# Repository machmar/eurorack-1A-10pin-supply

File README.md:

# eurorack-1A-10pin-supply
This is a eurorack PSU which uses two 3A PWM regulators like [these from Aliexpress](https://www.aliexpress.com/item/1005004052885353.html?spm=a2g0o.productlist.0.0.695838edDr9Fcs&algo_pvid=d174f836-2c64-4925-bf83-09754ddc93be&algo_exp_id=d174f836-2c64-4925-bf83-09754ddc93be-3&pdp_ext_f=%7B%22sku_id%22%3A%2212000027872810881%22%7D&pdp_npi=2%40dis%21CZK%21%2119.72%21%21%21%21%21%400b0a555916520957518301529e174a%2112000027872810881%21sea) and outputs +-12V DC.  
The output is only a 10 pin power bus.  
As the power source, use a AC transformer with two 12V or 15V secondary windings.  

As for the old files in this repo (1A PSU). I've disgned them over 4 years ago and back then I had no idea how to make good PCBs (not saying this new PCB is something amazing). I feel bad deleting them so I'll leave them here but **DO NOT BUILD THE OLD FILES!**.

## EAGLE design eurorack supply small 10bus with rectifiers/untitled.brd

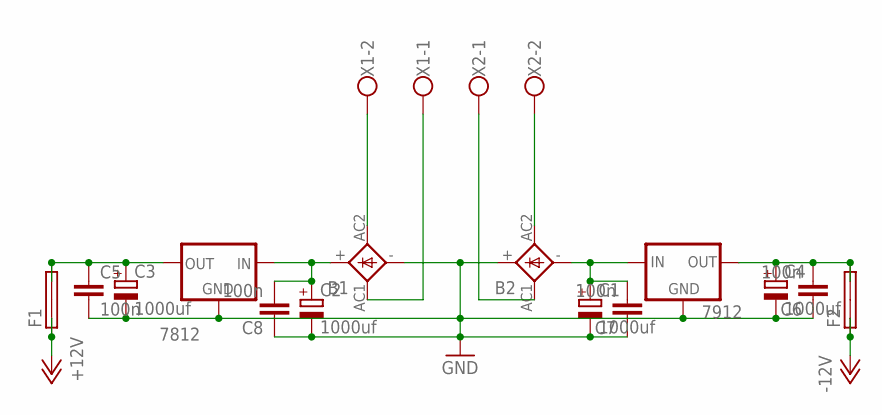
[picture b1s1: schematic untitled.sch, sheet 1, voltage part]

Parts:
7812: 79XXS
7912: 78XXS
B1, B2: FB15
C1, C2, C3, C4: 1000uf; TT5D11
C5, C6, C7, C8: 100n; C075-032X103
F1, F2: SHK20L
X1, X2: W237-102

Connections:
+12V: F1.1A, F1.1B; also elsewhere on the board
-12V: F2.1A, F2.1B; also elsewhere on the board
GND: 7812.GND, 7912.GND, B1.-, B2.+, C1.-, C2.-, C3.-, C4.-, C5.2, C6.1, C7.1, C8.1; also elsewhere on the board
unnamed: 7912.IN, B2.-, C1.+, C7.2
unnamed: 7812.IN, B1.+, C2.+, C8.2
unnamed: 7912.OUT, C4.+, C6.2, F2.2A, F2.2B
unnamed: 7812.OUT, C3.+, C5.1, F1.2A, F1.2B
unnamed: B1.AC2, X1.2
unnamed: B2.AC2, X2.2
unnamed: B1.AC1, X1.1
unnamed: B2.AC1, X2.1

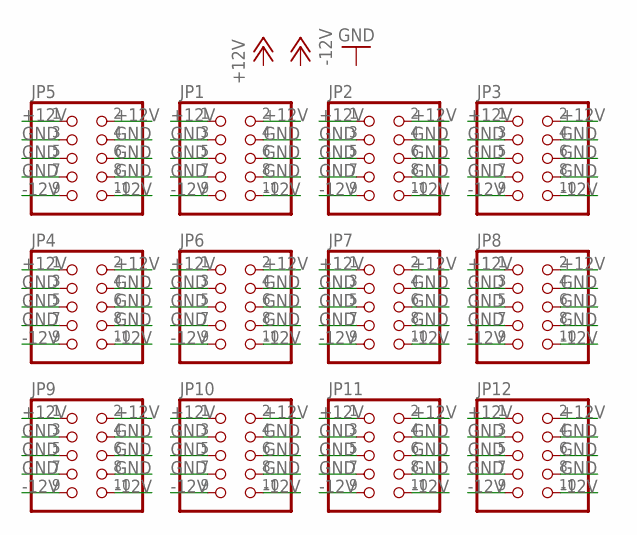
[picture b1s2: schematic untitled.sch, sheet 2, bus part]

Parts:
JP1, JP2, JP3, JP4, JP5, JP6, JP7, JP8, JP9, JP10, JP11, JP12: PINHD-2X5; 2X05

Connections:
+12V: JP1.1, JP1.2, JP2.1, JP2.2, JP3.1, JP3.2, JP4.1, JP4.2, JP5.1, JP5.2, JP6.1, JP6.2, JP7.1, JP7.2, JP8.1, JP8.2, JP9.1, JP9.2, JP10.1, JP10.2, JP11.1, JP11.2, JP12.1, JP12.2; also elsewhere on the board
-12V: JP1.9, JP1.10, JP2.9, JP2.10, JP3.9, JP3.10, JP4.9, JP4.10, JP5.9, JP5.10, JP6.9, JP6.10, JP7.9, JP7.10, JP8.9, JP8.10, JP9.9, JP9.10, JP10.9, JP10.10, JP11.9, JP11.10, JP12.9, JP12.10; also elsewhere on the board
GND: JP1.3, JP1.4, JP1.5, JP1.6, JP1.7, JP1.8, JP2.3, JP2.4, JP2.5, JP2.6, JP2.7, JP2.8, JP3.3, JP3.4, JP3.5, JP3.6, JP3.7, JP3.8, JP4.3, JP4.4, JP4.5, JP4.6, JP4.7, JP4.8, JP5.3, JP5.4, JP5.5, JP5.6, JP5.7, JP5.8, JP6.3, JP6.4, JP6.5, JP6.6, JP6.7, JP6.8, JP7.3, JP7.4, JP7.5, JP7.6, JP7.7, JP7.8, JP8.3, JP8.4, JP8.5, JP8.6, JP8.7, JP8.8, JP9.3, JP9.4, JP9.5, JP9.6, JP9.7, JP9.8, JP10.3, JP10.4, JP10.5, JP10.6, JP10.7, JP10.8, JP11.3, JP11.4, JP11.5, JP11.6, JP11.7, JP11.8, JP12.3, JP12.4, JP12.5, JP12.6, JP12.7, JP12.8; also elsewhere on the board

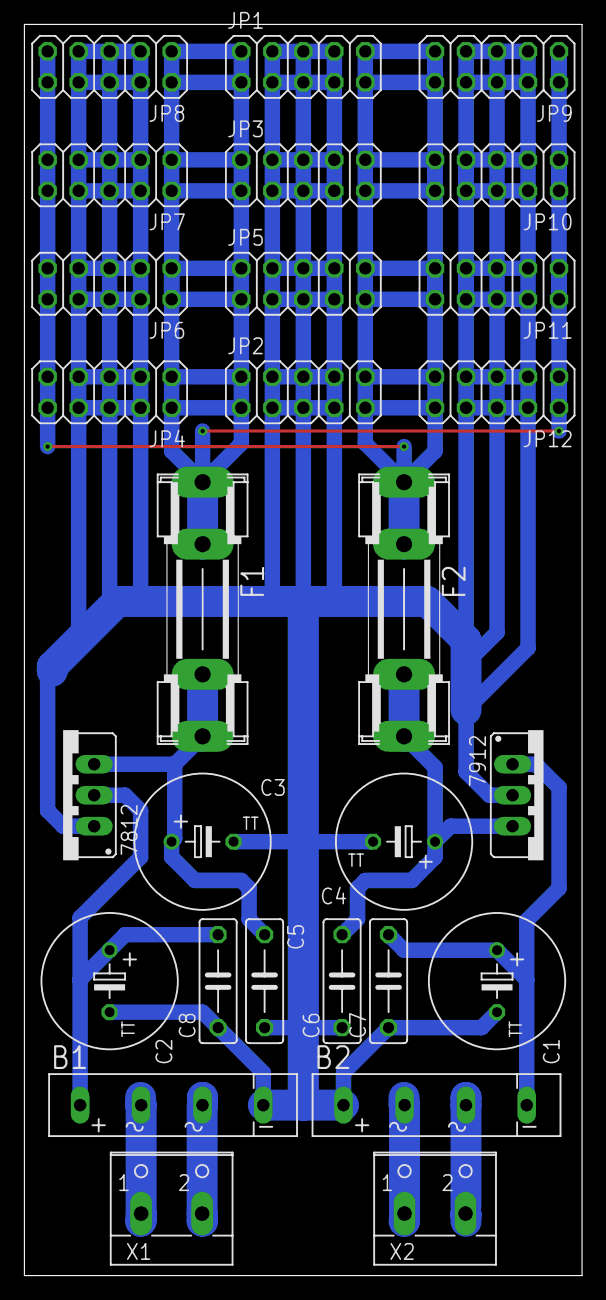
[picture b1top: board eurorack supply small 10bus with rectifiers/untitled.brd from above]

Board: 2 copper layers, 45.7 x 102.5 mm, 28 parts (0 on the bottom side), 11 nets.

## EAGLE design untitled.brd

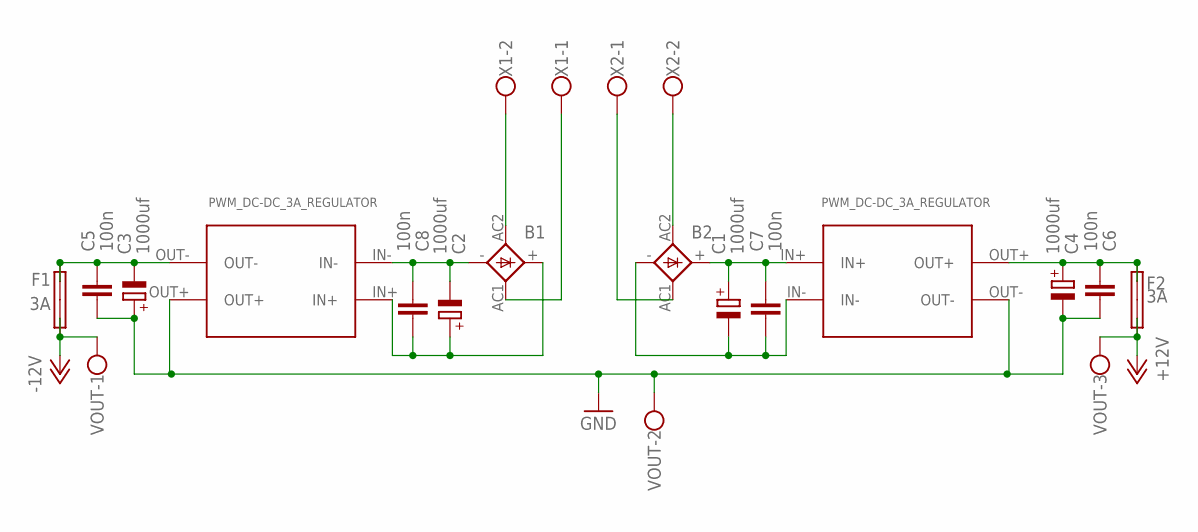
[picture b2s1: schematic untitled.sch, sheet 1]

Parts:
B1, B2: FB15
C1, C2, C3, C4: 1000uf; TT5D11
C5, C6, C7, C8: 100n; C075-032X103
F1, F2: 3A; SHK20L
PWM_DC-DC_3A_REGULATOR1, PWM_DC-DC_3A_REGULATOR2: CP8-ADJ
VOUT: W237-103
X1, X2: W237-102

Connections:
+12V: F2.1A, F2.1B, VOUT.3; also elsewhere on the board
-12V: F1.1A, F1.1B, VOUT.1; also elsewhere on the board
GND: C3.+, C4.-, C5.2, C6.1, PWM_DC-DC_3A_REGULATOR1.OUT+, PWM_DC-DC_3A_REGULATOR2.OUT-, VOUT.2; also elsewhere on the board
unnamed: B2.+, C1.+, C7.2, PWM_DC-DC_3A_REGULATOR2.IN+
unnamed: B1.-, C2.-, C8.2, PWM_DC-DC_3A_REGULATOR1.IN-
unnamed: B2.-, C1.-, C7.1, PWM_DC-DC_3A_REGULATOR2.IN-
unnamed: C4.+, C6.2, F2.2A, F2.2B, PWM_DC-DC_3A_REGULATOR2.OUT+
unnamed: C3.-, C5.1, F1.2A, F1.2B, PWM_DC-DC_3A_REGULATOR1.OUT-
unnamed: B1.AC2, X1.2
unnamed: B2.AC2, X2.2
unnamed: B1.AC1, X1.1
unnamed: B2.AC1, X2.1
unnamed: B1.+, C2.+, C8.1, PWM_DC-DC_3A_REGULATOR1.IN+

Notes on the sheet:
PWM_DC-DC_3A_REGULATOR

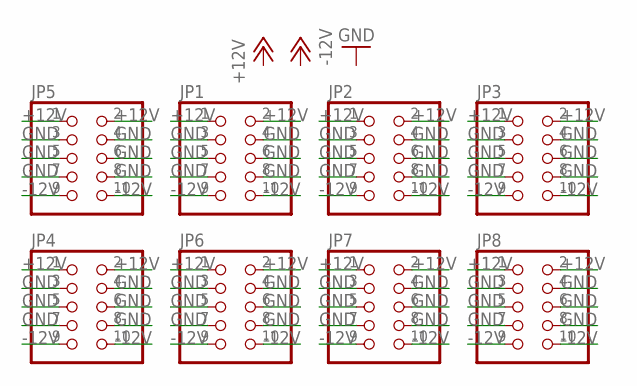
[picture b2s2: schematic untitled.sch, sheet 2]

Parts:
JP1, JP2, JP3, JP4, JP5, JP6, JP7, JP8: PINHD-2X5; 2X05

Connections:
+12V: JP1.1, JP1.2, JP2.1, JP2.2, JP3.1, JP3.2, JP4.1, JP4.2, JP5.1, JP5.2, JP6.1, JP6.2, JP7.1, JP7.2, JP8.1, JP8.2; also elsewhere on the board
-12V: JP1.9, JP1.10, JP2.9, JP2.10, JP3.9, JP3.10, JP4.9, JP4.10, JP5.9, JP5.10, JP6.9, JP6.10, JP7.9, JP7.10, JP8.9, JP8.10; also elsewhere on the board
GND: JP1.3, JP1.4, JP1.5, JP1.6, JP1.7, JP1.8, JP2.3, JP2.4, JP2.5, JP2.6, JP2.7, JP2.8, JP3.3, JP3.4, JP3.5, JP3.6, JP3.7, JP3.8, JP4.3, JP4.4, JP4.5, JP4.6, JP4.7, JP4.8, JP5.3, JP5.4, JP5.5, JP5.6, JP5.7, JP5.8, JP6.3, JP6.4, JP6.5, JP6.6, JP6.7, JP6.8, JP7.3, JP7.4, JP7.5, JP7.6, JP7.7, JP7.8, JP8.3, JP8.4, JP8.5, JP8.6, JP8.7, JP8.8; also elsewhere on the board

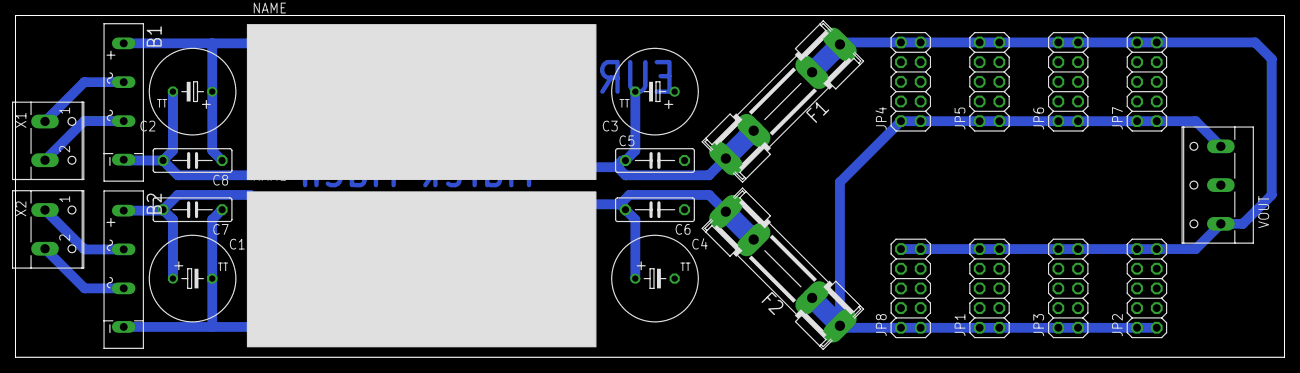
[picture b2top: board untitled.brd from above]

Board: 2 copper layers, 163.8 x 44.1 mm, 25 parts (0 on the bottom side), 13 nets.

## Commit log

2022-05-09 Edited for new files
2022-05-09 Added actually good files
2022-05-09 wrong directory
2022-05-09 moved the PCB to the correct directory
2022-05-09 added image previews
    so it's easier to browse through this repo!
2022-05-09 added a picture of the PCB
